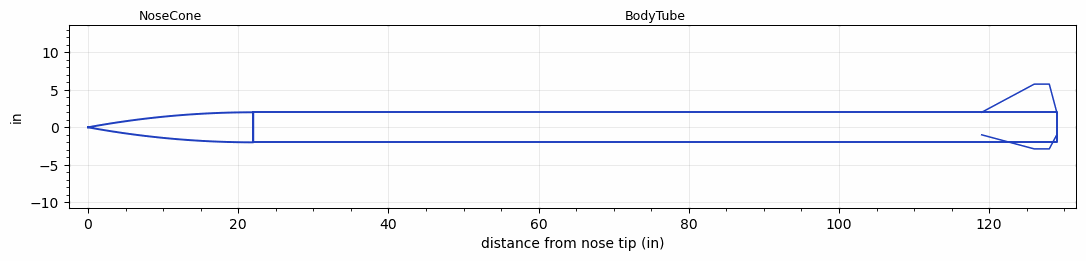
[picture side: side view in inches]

<RASAeroDocument>
 <FileVersion>2</FileVersion>
 <RocketDesign>
  <NoseCone>
   <Length>22</Length>
   <Diameter>4</Diameter>
   <Shape>Tangent Ogive</Shape>
   <Location>0</Location>
  </NoseCone>
  <BodyTube>
   <Length>107</Length>
   <Diameter>4</Diameter>
   <Location>22</Location>
   <Fin>
    <Count>3</Count>
    <Chord>10</Chord>
    <Span>3.75</Span>
    <SweepDistance>7</SweepDistance>
    <TipChord>2</TipChord>
    <Thickness>0.25</Thickness>
    <LERadius>0.125</LERadius>
    <Location>10</Location>
    <AirfoilSection>Double Wedge</AirfoilSection>
    <FX1>1</FX1>
    <FX3>1</FX3>
   </Fin>
  </BodyTube>
  <Surface>Smooth Paint</Surface>
  <ModifiedBarrowman>False</ModifiedBarrowman>
  <Turbulence>False</Turbulence>
  <UseBooster1>False</UseBooster1>
  <UseBooster2>False</UseBooster2>
 </RocketDesign>
 <LaunchSite>
  <Altitude>5000</Altitude>
  <Pressure>0</Pressure>
  <RodAngle>0</RodAngle>
  <RodLength>4</RodLength>
  <Temperature>95</Temperature>
  <WindSpeed>0</WindSpeed>
 </LaunchSite>
 <Recovery>
  <Altitude1>1000</Altitude1>
  <Altitude2>1000</Altitude2>
  <DeviceType1>None</DeviceType1>
  <DeviceType2>None</DeviceType2>
  <Event1>False</Event1>
  <Event2>False</Event2>
  <Size1>1</Size1>
  <Size2>1</Size2>
  <EventType1>None</EventType1>
  <EventType2>None</EventType2>
  <CD1>1.33</CD1>
  <CD2>1.33</CD2>
 </Recovery>
 <SimulationList>
  <Simulation>
   <SustainerEngine>N2540-GR-P  (CTI)</SustainerEngine>
   <SustainerLaunchWt>66</SustainerLaunchWt>
   <SustainerNozzleDiameter>1.5</SustainerNozzleDiameter>
   <SustainerCG>81</SustainerCG>
   <SustainerIgnitionDelay>0</SustainerIgnitionDelay>
   <Booster1SeparationDelay>0</Booster1SeparationDelay>
   <Booster1IgnitionDelay>0</Booster1IgnitionDelay>
   <IncludeBooster1>False</IncludeBooster1>
   <Booster2Delay>0</Booster2Delay>
   <IncludeBooster2>False</IncludeBooster2>
   <TimetoApogee>49.03778</TimetoApogee>
   <MaxAltitude>39931.58</MaxAltitude>
   <MaxVelocity>1981.196</MaxVelocity>
   <OptimumWt>65.625</OptimumWt>
   <OptimumMaxAlt>65.625</OptimumMaxAlt>
  </Simulation>
  <Simulation>
   <SustainerEngine>N1975-GR  (CTI)</SustainerEngine>
   <SustainerLaunchWt>60</SustainerLaunchWt>
   <SustainerNozzleDiameter>1.5</SustainerNozzleDiameter>
   <SustainerCG>80</SustainerCG>
   <SustainerIgnitionDelay>0</SustainerIgnitionDelay>
   <Booster1SeparationDelay>0</Booster1SeparationDelay>
   <Booster1IgnitionDelay>0</Booster1IgnitionDelay>
   <IncludeBooster1>False</IncludeBooster1>
   <Booster2Delay>0</Booster2Delay>
   <IncludeBooster2>False</IncludeBooster2>
   <TimetoApogee>44.06861</TimetoApogee>
   <MaxAltitude>30897.95</MaxAltitude>
   <MaxVelocity>1674.957</MaxVelocity>
  </Simulation>
  <Simulation>
   <SustainerEngine>N2501-WH-P  (CTI)</SustainerEngine>
   <SustainerLaunchWt>60</SustainerLaunchWt>
   <SustainerNozzleDiameter>1</SustainerNozzleDiameter>
   <SustainerCG>80</SustainerCG>
   <SustainerIgnitionDelay>0</SustainerIgnitionDelay>
   <Booster1SeparationDelay>0</Booster1SeparationDelay>
   <Booster1IgnitionDelay>0</Booster1IgnitionDelay>
   <IncludeBooster1>False</IncludeBooster1>
   <Booster2Delay>0</Booster2Delay>
   <IncludeBooster2>False</IncludeBooster2>
   <TimetoApogee>44.68851</TimetoApogee>
   <MaxAltitude>33836.06</MaxAltitude>
   <MaxVelocity>1808.059</MaxVelocity>
  </Simulation>
  <Simulation>
   <SustainerEngine>N2600-SK  (CTI)</SustainerEngine>
   <SustainerLaunchWt>60</SustainerLaunchWt>
   <SustainerNozzleDiameter>1</SustainerNozzleDiameter>
   <SustainerCG>80</SustainerCG>
   <SustainerIgnitionDelay>0</SustainerIgnitionDelay>
   <Booster1SeparationDelay>0</Booster1SeparationDelay>
   <Booster1IgnitionDelay>0</Booster1IgnitionDelay>
   <IncludeBooster1>False</IncludeBooster1>
   <Booster2Delay>0</Booster2Delay>
   <IncludeBooster2>False</IncludeBooster2>
   <TimetoApogee>36.17994</TimetoApogee>
   <MaxAltitude>21068.45</MaxAltitude>
   <MaxVelocity>1331.61</MaxVelocity>
  </Simulation>
  <Simulation>
   <SustainerEngine>N2850-BS  (CTI)</SustainerEngine>
   <SustainerLaunchWt>61</SustainerLaunchWt>
   <SustainerNozzleDiameter>1</SustainerNozzleDiameter>
   <SustainerCG>80</SustainerCG>
   <SustainerIgnitionDelay>0</SustainerIgnitionDelay>
   <Booster1SeparationDelay>0</Booster1SeparationDelay>
   <Booster1IgnitionDelay>0</Booster1IgnitionDelay>
   <IncludeBooster1>False</IncludeBooster1>
   <Booster2Delay>0</Booster2Delay>
   <IncludeBooster2>False</IncludeBooster2>
   <TimetoApogee>41.07911</TimetoApogee>
   <MaxAltitude>27991.46</MaxAltitude>
   <MaxVelocity>1606.195</MaxVelocity>
  </Simulation>
  <Simulation>
   <SustainerEngine>N2900-CL  (CTI)</SustainerEngine>
   <SustainerLaunchWt>61</SustainerLaunchWt>
   <SustainerNozzleDiameter>1</SustainerNozzleDiameter>
   <SustainerCG>80</SustainerCG>
   <SustainerIgnitionDelay>0</SustainerIgnitionDelay>
   <Booster1SeparationDelay>0</Booster1SeparationDelay>
   <Booster1IgnitionDelay>0</Booster1IgnitionDelay>
   <IncludeBooster1>False</IncludeBooster1>
   <Booster2Delay>0</Booster2Delay>
   <IncludeBooster2>False</IncludeBooster2>
   <TimetoApogee>48.98779</TimetoApogee>
   <MaxAltitude>41435.17</MaxAltitude>
   <MaxVelocity>2060.319</MaxVelocity>
  </Simulation>
 </SimulationList>
</RASAeroDocument>
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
